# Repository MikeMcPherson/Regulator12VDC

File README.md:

# Regulator12VDC
## This is a work in progress, not yet fully designed or tested...
This is the 12VDC (nominal) 50A buck-boost regulator that is an optional component of the PowerController12VDC remotely-manageable power distribution device for amateur radio.  (See other repository.)
## Features
- Buck-boost voltage regulator maintains constant output voltage over wide range of input voltages; default output voltage 13.8 VDC, configurable from 12.0-14.2 VDC

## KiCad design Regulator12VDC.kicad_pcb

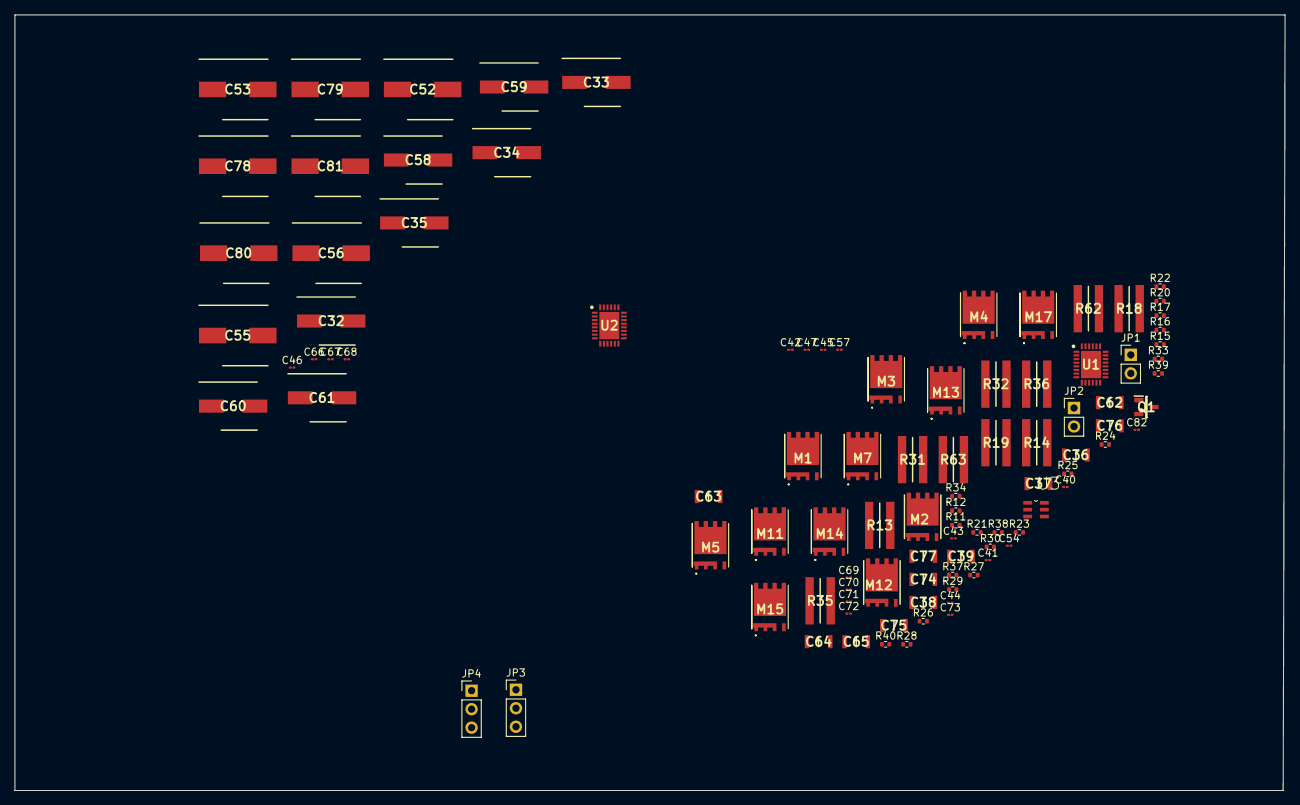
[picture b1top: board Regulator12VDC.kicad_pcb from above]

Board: 4 copper layers, 174.5 x 106.6 mm, 99 parts (0 on the bottom side), 54 nets, no tracks yet.

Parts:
C32, C33, C34, C35, C58, C59, C60, C61: EEE-FK1E330P; CAPAE660X610N
C36, C37, C38, C39, C62, C63, C64, C65: C3216X7R1H106K160AE; CAPC3216X180N
C40, C54, C57, C66, C70, C82: 1uF; C_01005_0402Metric
C41, C67: 0.47uF; C_01005_0402Metric
C42, C44, C46, C47, C68, C71, C73: 0.1uF; C_01005_0402Metric
C43, C69: 4.7uF; C_01005_0402Metric
C45: 3.3nF; C_01005_0402Metric
C52, C53, C55, C56, C78, C79, C80, C81: 16SVF560M; CAPAE830X1200N
C72: 47nF; C_01005_0402Metric
C74, C75, C76, C77: C3216X5R1C476M160AB; CAPC3216X180N
JP1, JP2: Jumper_2_Open; PinHeader_1x02_P2.54mm_Vertical
JP3, JP4: Jumper_3_Bridged12; PinHeader_1x03_P2.54mm_Vertical
M1, M5, M11, M15: BSC014N04LSI; BSC059N04LS6ATMA1
M2, M12: BSC010N04LSI; TDSON-8FL
M3, M7, M13, M17: BSC015NE2LS5I; BSC059N04LS6ATMA1
M4, M14: BSC009NE2LS5I; BSC059N04LS6ATMA1
Q1: BSS138L; SOT96P237X111-3N
R11, R12, R28, R29, R30: 100K; R_0402_1005Metric
R13, R14, R31, R32: KRL6432D-M-R002-G-T1; RESC3163X70N
R15: 3K; R_0402_1005Metric
R16, R34: 309K; R_0402_1005Metric
R17: 665K; R_0402_1005Metric
R18, R19, R35, R36, R62, R63: KRL6432D-M-R006-G-T1; RESC3163X50N
R20, R21: 50; R_0402_1005Metric
R22: 604K; R_0402_1005Metric
R23, R40: 49.9K; R_0402_1005Metric
R24, R26: 365K; R_0402_1005Metric
R25, R27: 56.2K; R_0402_1005Metric
R33: 8.2K; R_0402_1005Metric
R37, R38: 15; R_0402_1005Metric
R39: 638K; R_0402_1005Metric
U1, U2: LT8390AHUFD#PBF; QFN50P400X500X80-29N-D
U3: LTC6908HS6-2TRPBF; SOT95P280X100-6N

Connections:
/U1BG1: M2.4, U1.26
/U1BG2: M7.4, U1.25
/U1ENUVLO: Q1.3, R24.2, R25.1, R26.2, R27.1, U1.6, U2.6
/U1FB: JP4.2, U1.16
/U1INTVCC: C69.1, R30.2, U1.5
/U1ISMON: R28.1, U1.13, U2.10
/U1ISN: C82.1, R38.2, U1.12
/U1ISP: C82.2, R37.2, U1.11
/U1LSN: R31.2, R32.2, U1.3
/U1LSP: C68.1, M1.1, M1.2, M1.3, M2.5, M2.6, M2.7, M2.8, M5.1, M5.2, M5.3, R31.1, R32.1, U1.2, U1.28
/U1SW2: C73.1, M3.5, M3.6, M3.7, M3.8, M4.1, M4.2, M4.3, M7.5, M7.6, M7.7, M7.8, U1.23
/U1VOUT: C55.1, C56.1, C70.1, C74.1, C75.1, C76.1, C77.1, C78.1, C79.1, C80.1, C81.1, JP1.1, M4.5, M4.6, M4.7, M4.8, R18.2, R19.2, R21.1, R35.1, R36.1, R37.1, R62.1, R63.1, U1.21
/U2BG1: M12.4, U2.26
/U2BG2: M17.4, U2.25
/U2FB: JP3.2, U2.16
/U2INTVCC: C43.1, C47.1, R12.2, R17.1, U2.5, U3.1
/U2ISN: C54.1, R21.2, U2.12
/U2ISP: C54.2, R20.2, U2.11
/U2LSN: R13.2, R14.2, U2.3
/U2LSP: C42.1, M11.1, M11.2, M11.3, M12.5, M12.6, M12.7, M12.8, M15.1, M15.2, M15.3, R13.1, R14.1, U2.2, U2.28
/U2SW2: C46.1, M13.5, M13.6, M13.7, M13.8, M14.1, M14.2, M14.3, M17.5, M17.6, M17.7, M17.8, U2.23
/U2SYNC: U2.19, U3.5
/U2VOUT: C52.1, C53.1, C57.1, M14.5, M14.6, M14.7, M14.8, R18.1, R19.1, R20.1, U2.21
/U3OUT1: U1.19, U3.4, U3.6
/Vin: C32.1, C33.1, C34.1, C35.1, C36.1, C37.1, C38.1, C39.1, C40.1, C58.1, C59.1, C60.1, C61.1, C62.1, C63.1, C64.1, C65.1, C66.1, M1.5, M1.6, M1.7, M1.8, M5.5, M5.6, M5.7, M5.8, M11.5, M11.6, M11.7, M11.8, M15.5, M15.6, M15.7, M15.8, R24.1, R26.1, U1.4, U2.4
GND: C32.2, C33.2, C34.2, C35.2, C36.2, C37.2, C38.2, C39.2, C40.2, C41.2, C43.2, C44.2, C45.2, C52.2, C53.2, C55.2, C56.2, C57.2, C58.2, C59.2, C60.2, C61.2, C62.2, C63.2, C64.2, C65.2, C66.2, C67.2, C69.2, C70.2, C71.2, C72.2, C74.2, C75.2, C76.2, C77.2, C78.2, C79.2, C80.2, C81.2, M2.1, M2.2, M2.3, M3.1, M3.2, M3.3, M3.4, M7.1, M7.2, M7.3, M12.1, M12.2, M12.3, M13.1, M13.2, M13.3, M13.4, M17.1, M17.2, M17.3, Q1.2, R16.2, R23.2, R25.2, R27.2, R28.2, R34.2, R40.2, U1.7, U1.29, U2.7, U2.29
unnamed: C41.1, R11.2, U2.8, U2.9
unnamed: C42.2, U2.27
unnamed: C44.1, R11.1, U2.15
unnamed: C45.1, R15.2
unnamed: C46.2, U2.24
unnamed: C47.2, U3.2
unnamed: C67.1, R29.2, U1.8, U1.9
unnamed: C68.2, U1.27
unnamed: C71.1, U1.15
unnamed: C72.1, R33.2
unnamed: C73.2, U1.24
unnamed: JP2.1, R35.2, R36.2, R38.1, R62.2, R63.2
unnamed: JP1.2, R22.1
unnamed: JP2.2, R39.1
unnamed: JP3.1, R22.2, R23.1
unnamed: JP4.1, R39.2, R40.1
unnamed: M1.4, M5.4, U1.1
unnamed: M4.4, U1.22
unnamed: M11.4, M15.4, U2.1
unnamed: M14.4, U2.22
unnamed: R12.1, U2.14
unnamed: R15.1, U2.17
unnamed: R16.1, U2.18
unnamed: R17.2, U3.3
unnamed: R29.1, U1.10
unnamed: R30.1, U1.14
unnamed: R33.1, U1.17
unnamed: R34.1, U1.18
